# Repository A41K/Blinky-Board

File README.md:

Yeah so this is my blinky board for stasis. I actually made this because I really liked the Macropad and how you actually got the stuff
from HQ to build it and also I actually wanted to jump back into stasis because I started before, but I had other YSWS's on my table.

Th guide was really easy and on point so it wasnt a challenge

| Name                  | Purpose          | QTY            |
| ----------------------| -----------------| -------------  |
| NE555P                | IC               | 1              | 
| CD4017                | IC               | 1              |
| Capacitor             | --II--           | 1              | 
| Resistor              | --II--           | 2              | 
| Potentiometer         | --II--           | 1              | 
| LED                   | LED              | 50             | 
| Header                | --II--           | 2              |

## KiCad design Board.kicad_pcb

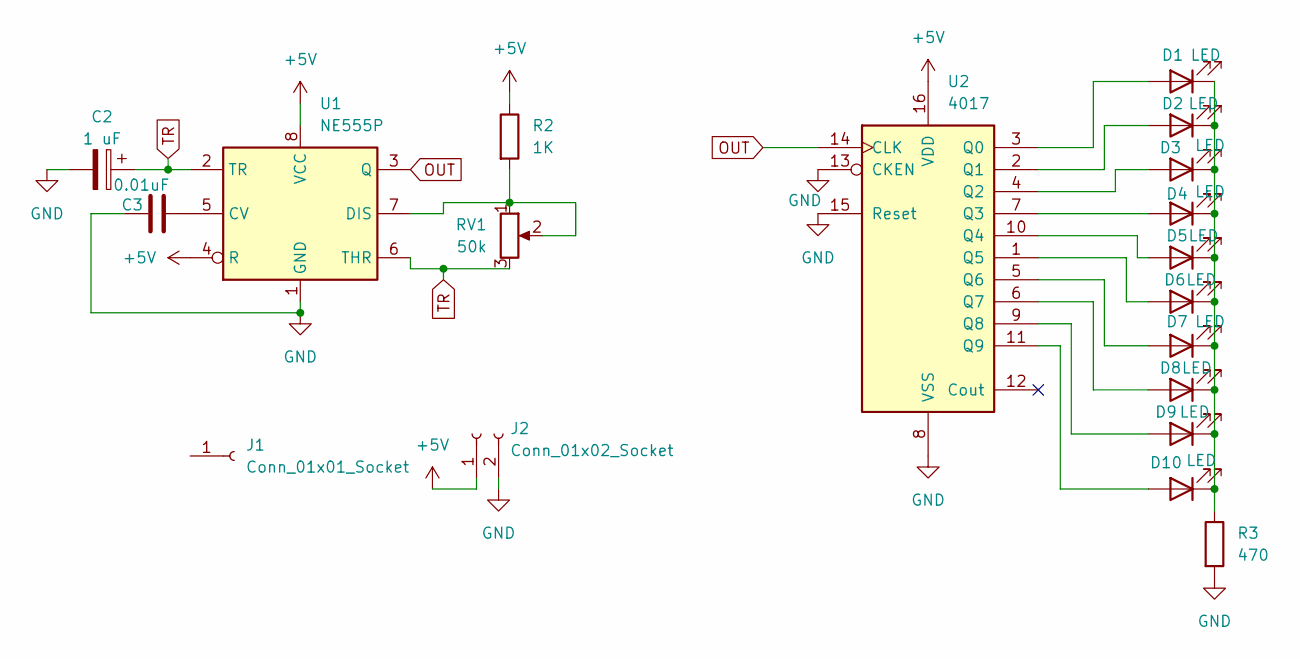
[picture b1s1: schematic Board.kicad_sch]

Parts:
C2: 1 uF; CP_Radial_D5.0mm_P2.00mm
C3: 0.01uF; C_Disc_D7.5mm_W2.5mm_P5.00mm
D1, D2, D3, D4, D5, D6, D7, D8, D9, D10: LED; LED_D3.0mm
J1: Conn_01x01_Socket; PinHeader_1x01_P2.54mm_Horizontal
J2: Conn_01x02_Socket; PinHeader_1x02_P2.54mm_Horizontal
R2: 1K; R_Axial_DIN0207_L6.3mm_D2.5mm_P7.62mm_Horizontal
R3: 470; R_Axial_DIN0207_L6.3mm_D2.5mm_P7.62mm_Horizontal
RV1: 50k; Potentiometer_Vishay_T93YA_Vertical
U1: NE555P; DIP-8_W7.62mm
U2: 4017; DIP794W45P254L1969H508Q16

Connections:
+5V: J2.1, R2.1, U1.4 (R), U1.8 (VCC), U2.16 (VDD)
GND: C2.2, C3.1, J2.2, R3.2, U1.1 (GND), U2.8 (VSS), U2.13 (CKEN), U2.15 (Reset)
unnamed: D1.2 (A), U2.3 (Q0)
unnamed: D1.1 (K), D2.1 (K), D3.1 (K), D4.1 (K), D5.1 (K), D6.1 (K), D7.1 (K), D8.1 (K), D9.1 (K), D10.1 (K), R3.1
unnamed: D2.2 (A), U2.2 (Q1)
unnamed: D3.2 (A), U2.4 (Q2)
unnamed: D4.2 (A), U2.7 (Q3)
unnamed: D5.2 (A), U2.10 (Q4)
unnamed: D6.2 (A), U2.1 (Q5)
unnamed: D7.2 (A), U2.5 (Q6)
unnamed: D8.2 (A), U2.6 (Q7)
unnamed: D9.2 (A), U2.9 (Q8)
unnamed: D10.2 (A), U2.11 (Q9)
unnamed: C3.2, U1.5 (CV)
unnamed: R2.2, RV1.1, RV1.2, U1.7 (DIS)
OUT: U1.3 (Q), U2.14 (CLK)
TR: C2.1, RV1.3, U1.2 (TR), U1.6 (THR)

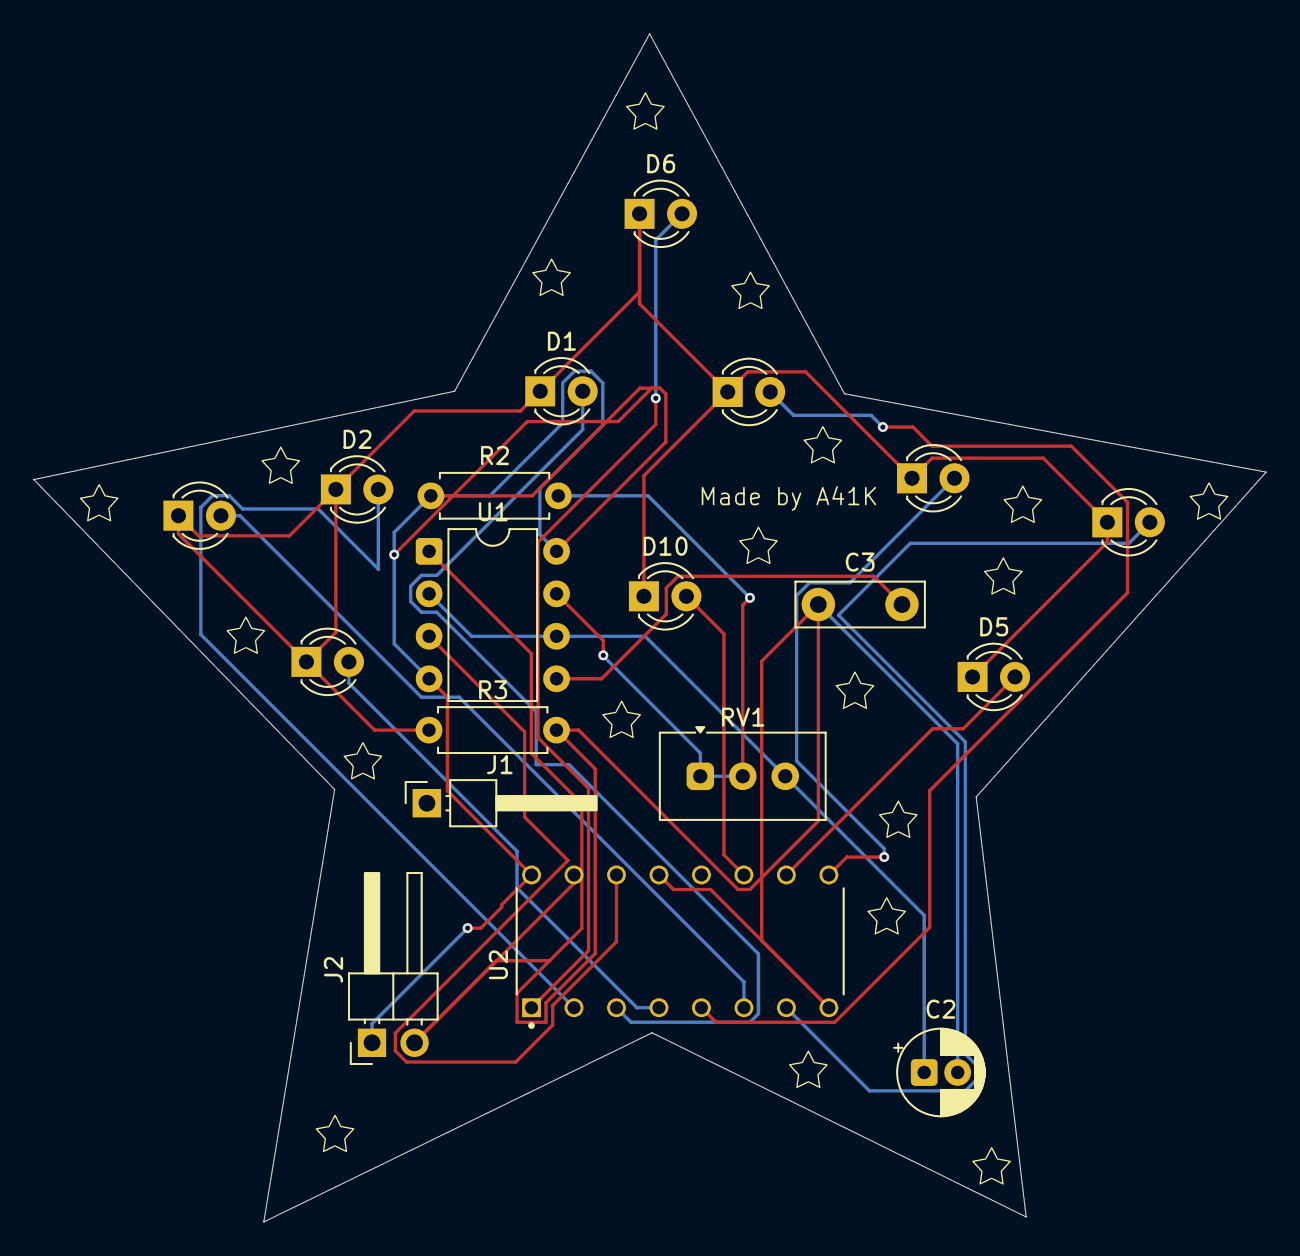
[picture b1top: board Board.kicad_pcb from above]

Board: 2 copper layers, 73.7 x 71.0 mm, 19 parts (0 on the bottom side), 17 nets.

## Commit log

2026-03-30 EVERYTHING IN ONE
2026-03-30 Add introduction and image to README
    Added a brief introduction and image for the Blinky board.
2026-03-30 step file
2026-03-31 Revise README with project details and parts list
    Updated project description and added components list.
2026-03-31 Fix typo and enhance README clarity
    Corrected a typo in the README and added a comment about the guide.
